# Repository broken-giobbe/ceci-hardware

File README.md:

# ceci-hardware
Hardware design files for our IoT sensor/actuator nodes based around the
ESP8266.

There are currently two hardware revisions:
 * rev0 (first prototype where sensor and actuator can be split)
 * rev1 (designed to act as a thermostat and fit into a vimar plana power box)

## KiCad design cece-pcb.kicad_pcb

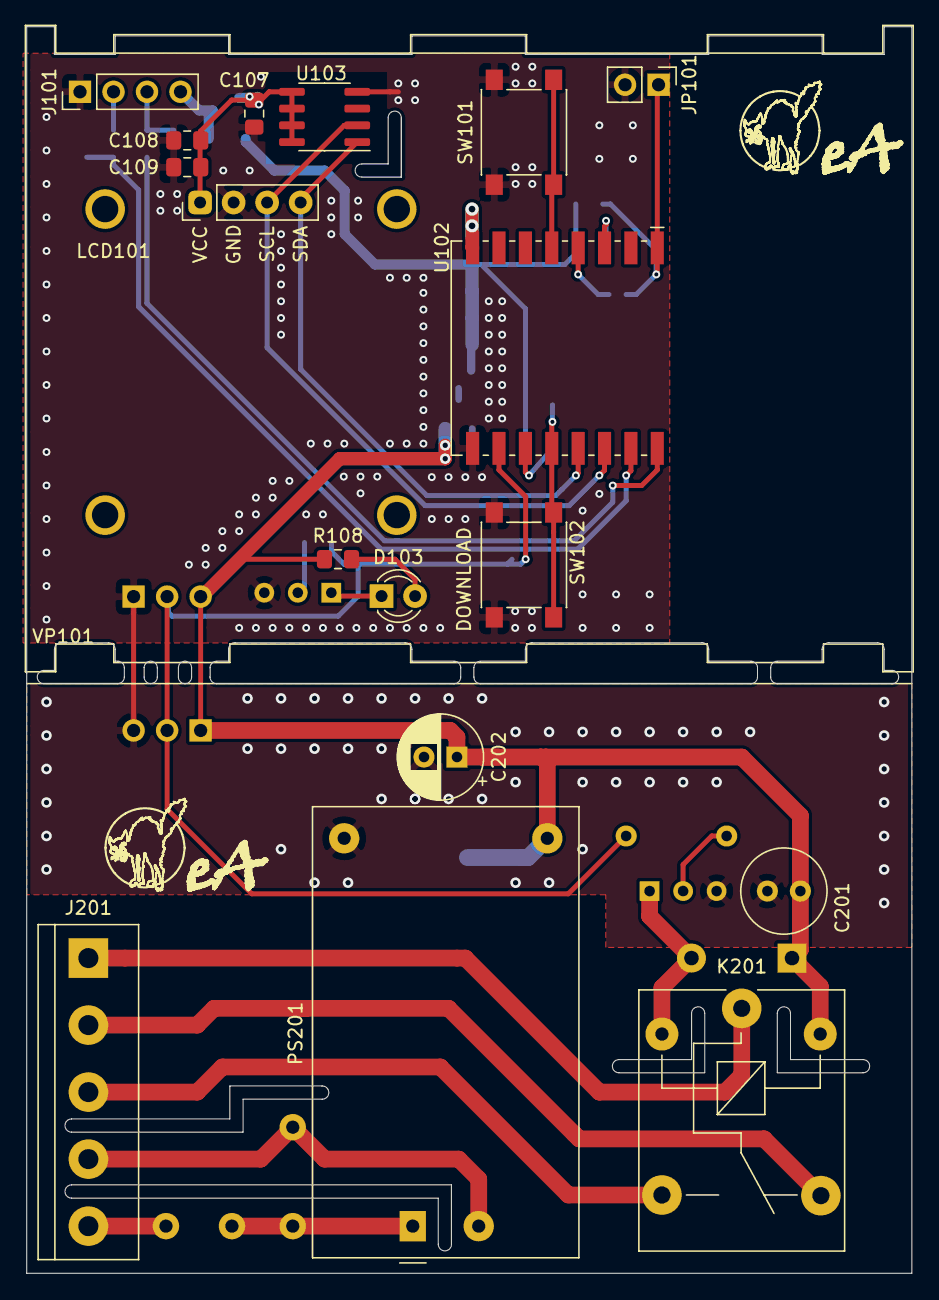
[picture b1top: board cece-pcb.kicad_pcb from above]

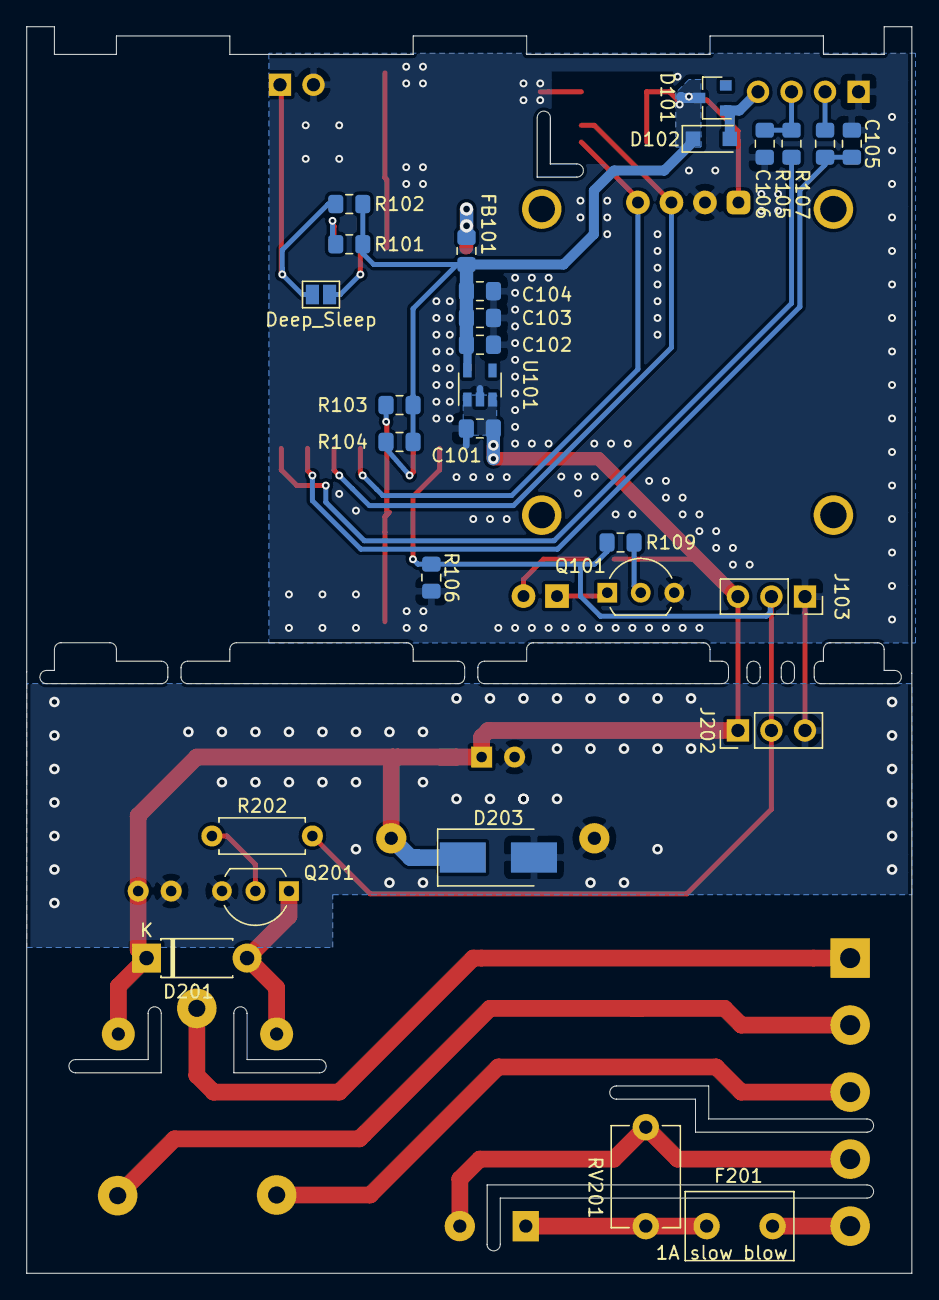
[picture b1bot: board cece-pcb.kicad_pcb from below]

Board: 2 copper layers, 67.0 x 94.5 mm, 48 parts (28 on the bottom side), 29 nets.

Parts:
C101, C103: 1u; C_0805_2012Metric_Pad1.15x1.40mm_HandSolder
C102, C108: 10u; C_0805_2012Metric_Pad1.15x1.40mm_HandSolder
C104, C107, C109: 100nF; C_0805_2012Metric_Pad1.15x1.40mm_HandSolder
C105, C106: 100p; C_0805_2012Metric_Pad1.15x1.40mm_HandSolder
C201: 10u; C_Radial_D6.3mm_H5.0mm_P2.50mm
C202: 100u; CP_Radial_D6.3mm_P2.50mm
D101: Schottky SOT-23; D_SOT-23_ANK
D102: Schottky SOD-123; D_SOD-123F
D103: LED; LED_D3.0mm
D201: 1N4001; D_DO-41_SOD81_P7.62mm_Horizontal
D203: SMBJ5.0A; D_SMB_Handsoldering
EA101, EA201: a_black_cat
F201: 1A slow blow; C_Disc_D8.0mm_W5.0mm_P5.00mm
FB101: Ferrite_Bead; R_0805_2012Metric_Pad1.15x1.40mm_HandSolder
J101: SERIAL; PinHeader_1x04_P2.54mm_Vertical
J103: Conn_01x03_Male; PinSocket_1x03_P2.54mm_Vertical
J201: VAC; TerminalBlock_bornier-5_P5.08mm
J202: Conn_01x03_Female; PinHeader_1x03_P2.54mm_Vertical
JP101: RST; PinHeader_1x02_P2.54mm_Vertical
JP103: Deep_Sleep; SolderJumper-2_P1.3mm_Open_Pad1.0x1.5mm
K201: SANYOU_SRD_Form_C; Relay_SPDT_SANYOU_SRD_Series_Form_C
LCD101: I2C_LCD_display; I2C_LCD_display_0.96
PS201: HLK-PM01; Converter_ACDC_HiLink_HLK-PMxx
Q101, Q201: Q_NPN; TO-92L_Inline_Wide
R101, R102, R103, R104, R106, R109: 10k; R_0805_2012Metric_Pad1.15x1.40mm_HandSolder
R105, R107, R108: 330; R_0805_2012Metric_Pad1.15x1.40mm_HandSolder
R202: 1k; R_Axial_DIN0207_L6.3mm_D2.5mm_P7.62mm_Horizontal
RV201: 10D561K; C_Disc_D7.5mm_W5.0mm_P7.50mm
SW101, SW102: SW_Push; SW_Push_1P1T_NO_6x6mm_H9.5mm
U101: TLV75533PDBV; SOT-23-5
U102: ESP-12F/ESP07; ESP-07
U103: LM75C; SOIC-8_3.9x4.9mm_P1.27mm
VP101: VimarPlana; vimar_plana_3P

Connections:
+3V3: C102.1, C103.1, C104.1, C107.1, C108.1, C109.1, D101.1, D102.1, FB101.2, LCD101.1, R101.2, R102.2, R103.2, R104.2, U101.5, U103.5, U103.6, U103.7, U103.8
+5V: C101.1, C201.1, C202.1, D201.1, D203.1, J103.3, J202.1, K201.5, PS201.4, R108.2, U101.1, U101.3
/Bottom Board/ACL: F201.2, J201.5
/Bottom Board/ACN: J201.4, PS201.2, RV201.2
/Bottom Board/C: J201.1, K201.1
/Bottom Board/NC: J201.2, K201.4
/Bottom Board/NO: J201.3, K201.3
/D0: JP103.2, U102.4
/D1|SCL: LCD101.3, U102.14, U103.2
/D2|SDA: LCD101.4, U102.13, U103.1
/D3: R103.1, SW102.1, U102.12
/D4: R104.1, U102.11
/D5|SCK: SW101.1, U102.5
/EN: R101.1, U102.3
/RST: JP101.1, JP103.1, R102.1, U102.1
/RX: C105.1, R107.2, U102.15
/TX: R105.2, U102.16
D8: J103.2, J202.2, R106.2, R109.2, R202.2, U102.10
GND: C101.2, C102.2, C103.2, C104.2, C105.2, C106.2, C107.2, C108.2, C109.2, C201.2, C202.2, D203.2, J101.1, J103.1, J202.3, JP101.2, LCD101.2, PS201.3, Q101.3, Q201.3, R106.1, SW101.2, SW102.2, U101.2, U102.9, U103.4
unnamed: C106.1, J101.3, R105.1
unnamed: D101.2, D102.2, J101.4
unnamed: D103.1, Q101.1
unnamed: D103.2, R108.1
unnamed: D201.2, K201.2, Q201.1
unnamed: F201.1, PS201.1, RV201.1
unnamed: FB101.1, U102.8
unnamed: J101.2, R107.1
unnamed: Q101.2, R109.1
unnamed: Q201.2, R202.1

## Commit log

2020-11-29 Add firmware and PCB files
2020-12-01 Complete ESP-12 part of the PCB
2020-12-04 Finish first board revision
2020-12-04 Make board DRC-friendly
2020-12-04 Hang the ESP8266 antenna outside of the board for better RF performance
2020-12-04 More touches to the layout. Almost finished
2020-12-04 better grounding layout for regulator ICs
2020-12-05 Add jumper to send 5V directly to the LDO if no battery is installed
2020-12-05 Add rescue ifles
2020-12-06 Add gerber files
2020-12-30 Fix wrong footprint for the pin headers
2021-01-06 Create gerbers with the fixed pin header size
2021-02-03 Update component values
2021-02-03 Update schematic references to reflect hierarchy
2021-02-04 Boards have arrived. Fixed the many mistakes in the schematic
2021-02-04 Update PCB
2021-02-09 Increase thermal relief size for easier hand soldering
2021-02-12 Add diode to protect the seral input when 3V3 are already supplied internally and shuffle stuff around a bit on the layout
2021-02-13 Add octave simulation files to test the heating algorithms
2021-02-22 Add resistor to limit peak current in the reset pushbutton. Prevents contact welding
2021-03-01 Add EA cat signature
2021-03-26 Use new stuff from pol lib
2021-04-08 Add .gitignore and README files
2021-04-08 Rename gerber files folder
2021-04-08 Draft layout for the new HW revision (just for show)
2021-04-11 Improve ACDC converter design to make it more robust
2021-04-12 Separate top and bottom PCBs
2021-04-12 Start defining PCB
2021-07-15 Complete the PCB ready for final review
2021-07-16 Fix slots shape
2021-08-11 Plot gerber files
2021-08-11 Fix minor PCB mistakes and bump up the version to 1.01
2021-08-13 Fix diode in the wrong direction and increase PCB revision to 1.02
2022-04-16 Update project to kicad 6 and move some components around
